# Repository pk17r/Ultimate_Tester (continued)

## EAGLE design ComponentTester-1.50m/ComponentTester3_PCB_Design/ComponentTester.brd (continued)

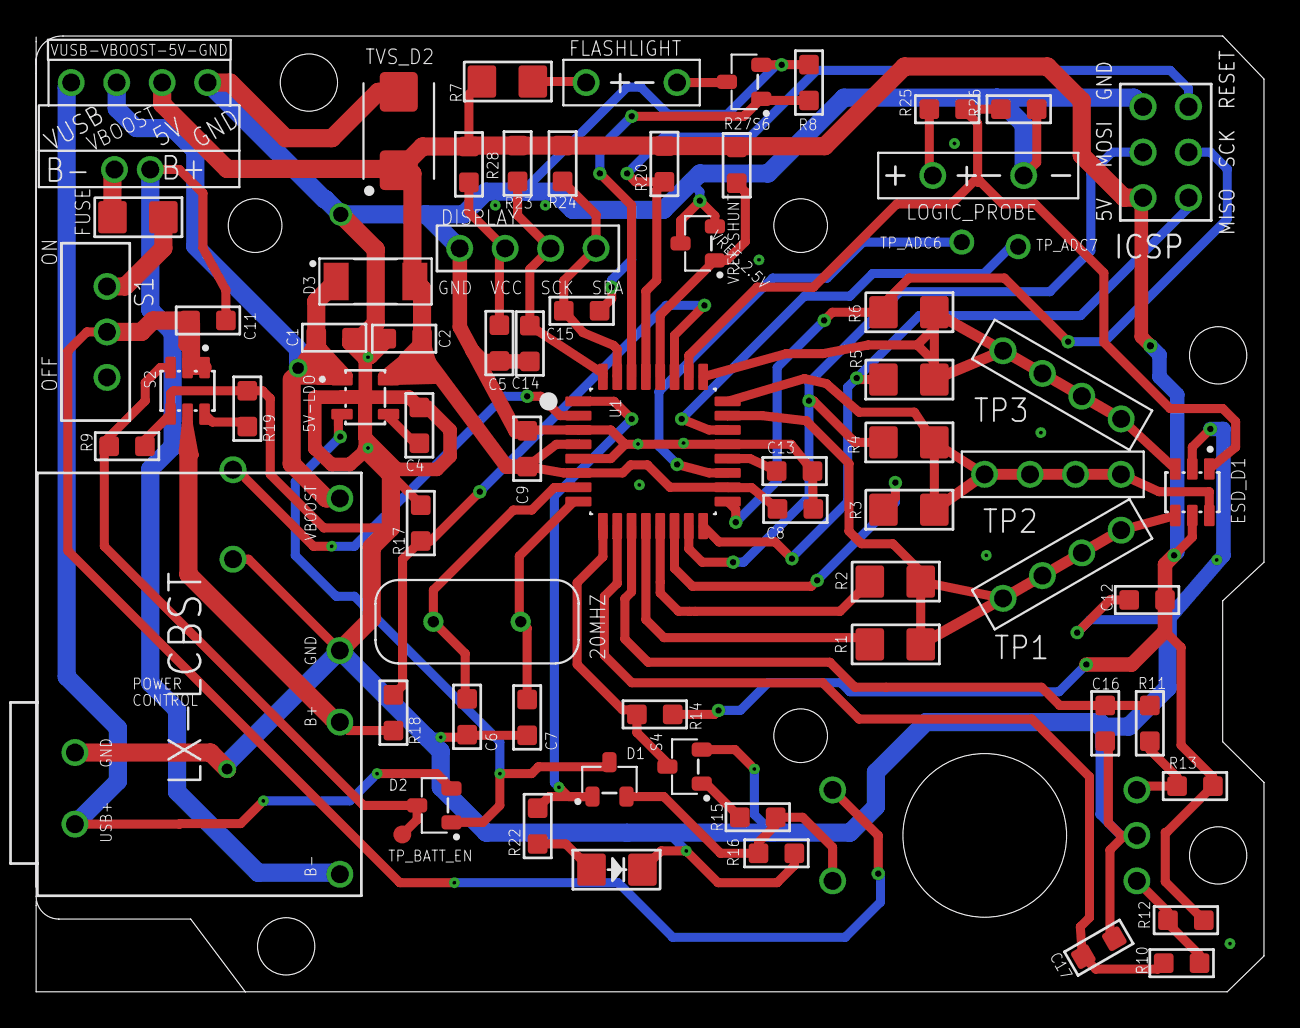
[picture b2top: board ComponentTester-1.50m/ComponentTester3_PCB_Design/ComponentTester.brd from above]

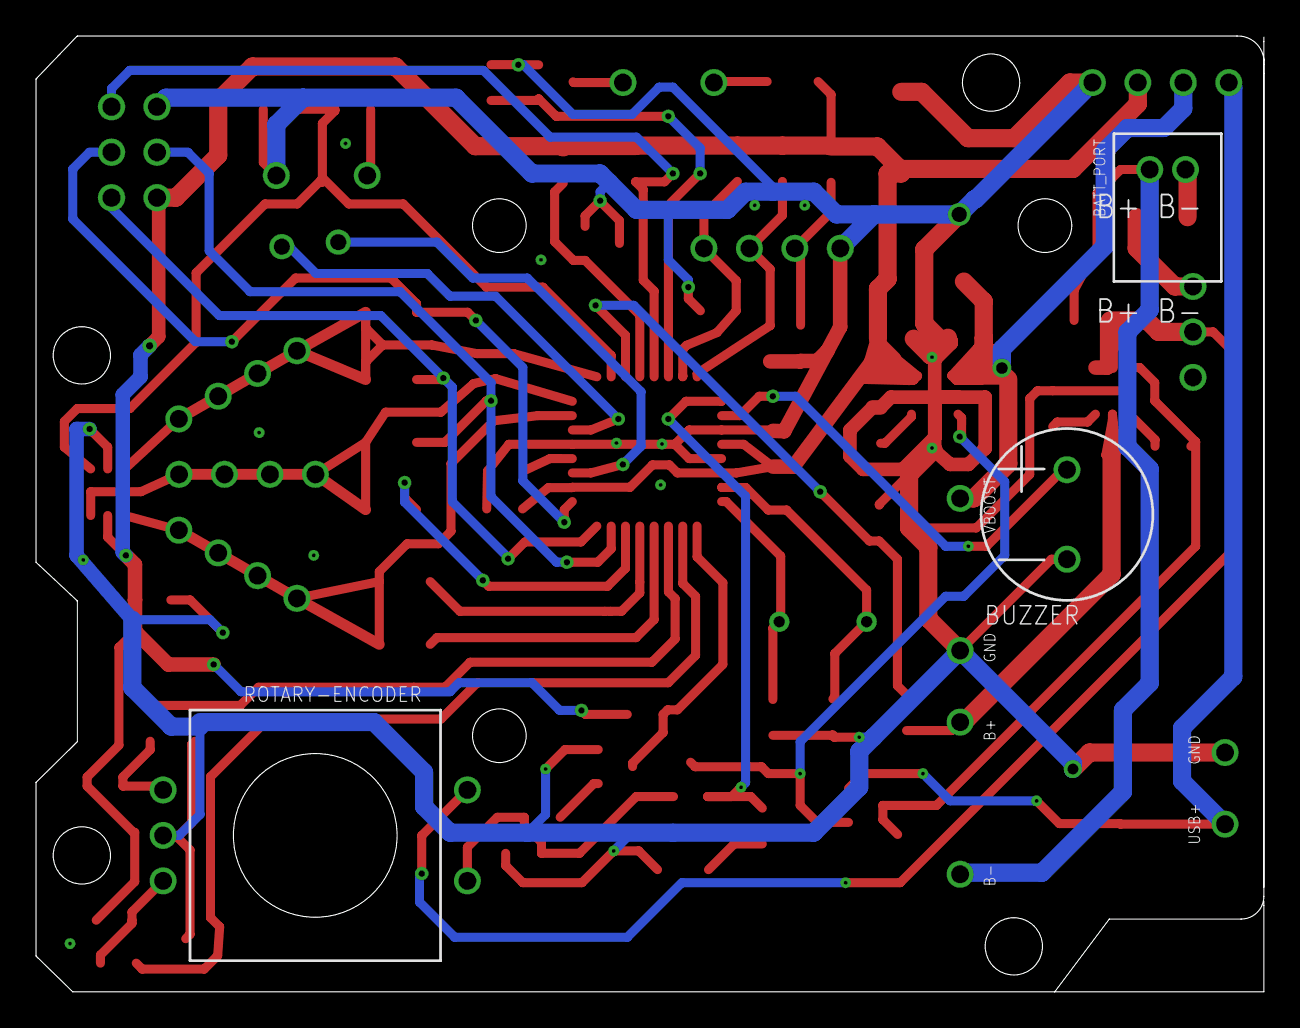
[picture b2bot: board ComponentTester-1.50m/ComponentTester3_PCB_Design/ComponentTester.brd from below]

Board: 2 copper layers, 68.6 x 53.4 mm, 72 parts (2 on the bottom side), 48 nets.

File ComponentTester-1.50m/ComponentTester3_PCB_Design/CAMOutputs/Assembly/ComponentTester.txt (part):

Partlist exported from D:/MyProjects/EAGLE/projects/ComponentTester3/ComponentTester.sch at 08-Nov-23 10:42 PM

Qty Value                         Device                                   Package                               Parts                                            Description                                                           AVAILABILITY CHECK_PRICES                                                                                 DATASHEET                                                         DESCRIPTION                                                                          DIGIKEY_PART_NUMBER    LOCATION MF                MP                 PACKAGE                    POS PRICE PURCHASE-URL                                                                                                                                                    SNAPEDA_LINK                                                                                  VALUE         
1                                 BATTERY-CHARGER-BOOST-MODULE-LX-LCBST    BATTERY-CHARGER-BOOST-MODULE-LX-LCBST CHARGE_BOOST                                     LX-LCBST_LIPO_CHARGER_BOOST                                                                                                                                                                                                                                                                                                                                                                                                                                                                                                                                                                                                                                                                                                  
1                                 DISPLAY-1.3"-SH1106-I2C                  DISPLAY-1.3"-SH1106-I2C               DISPLAY                                          SH1106 I2C DISPLAY                                                                                                                                                                                                                                                                                                                                                                                                                                                                                                                                                                                                                                                                                                           
2   100K                          RESISTOR_SMD0603                         0603                                  R8, R14                                          resistor smd                                                                                                                                                                                                                                                                                                                                                                                                                                                                                                                                                                                                                                                                                                                 
1   100K(OP)                      RESISTOR_SMD0603                         0603                                  R9                                               resistor smd                                                                                                                                                                                                                                                                                                                                                                                                                                                                                                                                                                                                                                                                                                                 
4   100nF                         CAPACITOR_SMD0603                        0603                                  C8, C9, C16, C17                                 capacitor 1206                                                                                                                                                                                                                                                                                                                                                                                                                                                                                                                                                                                                                                                                                                               
10  10K                           RESISTOR_SMD0603                         0603                                  R10, R11, R12, R13, R15, R18, R19, R20, R25, R27 resistor smd                                                                                                                                                                                                                                                                                                                                                                                                                                                                                                                                                                                                                                                                                                                 
1   10nF-C0G-NP0                  CAPACITOR_SMD0603                        0603                                  C4                                               capacitor 1206                                                                                                                                                                                                                                                                                                                                                                                                                                                                                                                                                                                                                                                                                                               
1   10uF                          CAPACITOR_SMD0603                        0603                                  C12                                              capacitor 1206                                                                                                                                                                                                                                                                                                                                                                                                                                                                                                                                                                                                                                                                                                               
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
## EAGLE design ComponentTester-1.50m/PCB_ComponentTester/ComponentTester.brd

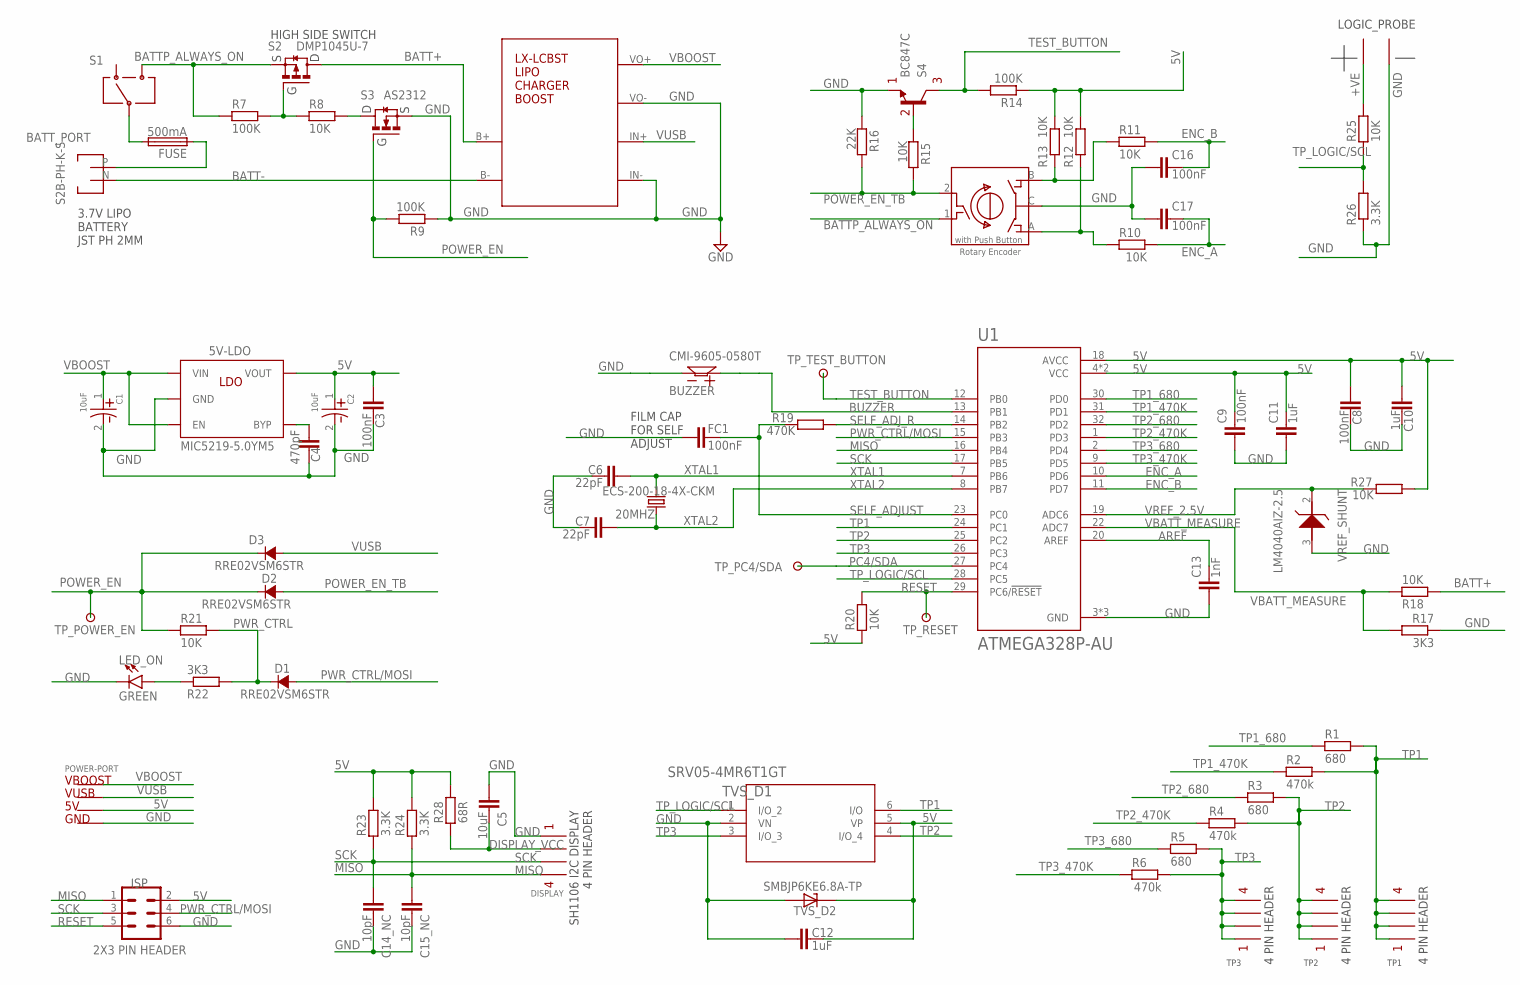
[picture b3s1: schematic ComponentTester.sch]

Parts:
5V-LDO: MIC5219-5.0YM5; SOT-23-5
20MHZ: ECS-200-18-4X-CKM; XTAL_ECS-200-18-4X-CKM
BATT_PORT: S2B-PH-K-S
BUZZER: CMI-9605-0580T; BUZZER_CMI-9605-0580T
C1, C2: 10uF; 1206_DIRECTED
C3, C16, C17: 100nF; 0603
C4: 470pF; 0603
C5: 10uF; 0603
C6, C7: 22pF; 0603
C8, C9: 100nF; 1206
C10, C11: 1uF; 1206
C12: 1uF; 0603
C13: 1nF; 0603
C14_NC, C15_NC: 10pF; 0603
CHARGE_BOOST: LX-LCBST_LIPO_CHARGER_BOOST
D1, D2, D3: RRE02VSM6STR; TUMD2SM-2
DISPLAY: SH1106_I2C_DISPLAY; SH1106_1.3IN_I2C_DISPLAY
ENC: PEC12R-3217F-S0024-ND; PEC12R-3217F-S0024
FC1: 100nF; 0805
FUSE: 500mA; 1206
ISP: 2X3 PIN HEADER; ISP_HEADER
LED_ON: GREEN; 1206_DIODE
LOGIC_PROBE: 5MM_PIN_HEADER
POWER-PORT: POWER_OUT_4_PIN_HEADER
R1, R3, R5: 680; 1206
R2, R4, R6: 470k; 1206
R7, R9, R14: 100K; 0603
R8, R10, R11, R12, R13, R15, R18, R20, R21, R27: 10K; 0603
R16: 22K; 0603
R17, R22: 3K3; 0603
R19: 470K; 0603
R23, R24: 3.3K; 0603
R25: 10K; 1206
R26: 3.3K; 1206
R28: 68R; 0603
S1: SLW-913535-2A-RA-D
S2: DMP1045U-7; SOT-23-3
S3: AS2312; SOT-23-3
S4: BC847C; SOT-23-3
TP1, TP2, TP3: 4_PIN_HEADER
TP_PC4/SDA: TEST_POINT
TP_POWER_EN: TEST_POINT
TP_RESET: TEST_POINT
TP_TEST_BUTTON: TEST_POINT
TVS_D1: SRV05-4MR6T1GT; TSOP6_3P1X1P7_ONS
TVS_D2: SMBJP6KE6.8A-TP; DIOM5336X244N
U1: ATMEGA328P-AU; QFP80P900X900X120-32N
VREF_SHUNT: LM4040AIZ-2.5; TO92-3

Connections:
5V: 5V-LDO.5 (VOUT), C2.1, C3.2, C8.2, C9.1, C10.2, C11.1, C12.1, ISP.2, POWER-PORT.5V, R12.2, R13.2, R14.1, R20.1, R23.2, R24.2, R27.1, R28.2, TVS_D1.5 (VP), TVS_D2.C, U1.4 (VCC), U1.6 (VCC), U1.18 (AVCC)
+VE: LOGIC_PROBE.P$1, R25.2
AREF: C13.1, U1.20 (AREF)
BATT+: CHARGE_BOOST.B+, R18.2, S2.3 (D)
BATT+_PORT: BATT_PORT.P, FUSE.1
BATT-: BATT_PORT.N, CHARGE_BOOST.B-
BATTP_ALWAYS_ON: ENC.1, R7.1, S1.3, S2.2 (S)
BUZZER: BUZZER.P$1, U1.13 (PB1)
BYP: 5V-LDO.4 (BYP), C4.2
DISPLAY_VCC: C5.1, DISPLAY.VCC, R28.1
ENC_A: C17.1, R10.2, U1.10 (PD6)
ENC_B: C16.1, R11.2, U1.11 (PD7)
FUSE_2_SWITCH: FUSE.2, S1.2
GND: 5V-LDO.2 (GND), BUZZER.P$2, C1.2 (N), C2.2 (N), C3.1, C4.1, C5.2, C6.1, C7.1, C8.1, C9.2, C10.1, C11.2, C12.2, C13.2, C14_NC.1, C15_NC.1, C16.2, C17.2, CHARGE_BOOST.IN- (USB-), CHARGE_BOOST.VO-, DISPLAY.GND, ENC.C, FC1.1, ISP.6, LED_ON.C, LOGIC_PROBE.P$2, POWER-PORT.GND, R9.1, R16.1, R17.1, R26.1, S3.2 (S), S4.2 (E), TVS_D1.2 (VN), TVS_D2.A, U1.3 (GND), U1.5 (GND), U1.21 (GND), VREF_SHUNT.3 (A)
MISO: C15_NC.2, DISPLAY.SDA, ISP.1, R24.1, U1.16 (PB4)
unnamed: ENC.B, R11.1, R13.1
unnamed: ENC.A, R10.1, R12.1
unnamed: R15.1, S4.1 (B)
NMOS_DRAIN: R8.2, S3.3 (D)
PC4/SDA: TP_PC4/SDA.P$1, U1.27 (PC4)
PMOS_GATE: R7.2, R8.1, S2.1 (G)
POWER_EN: D2.C, D3.C, R9.2, R21.1, S3.1 (G), TP_POWER_EN.P$1
POWER_EN_TB: D2.A, ENC.2, R15.2, R16.2
PWR_CTRL: D1.C, R21.2, R22.2
PWR_CTRL/MOSI: D1.A, ISP.4, U1.15 (PB3)
RESET: ISP.5, R20.2, TP_RESET.P$1, U1.29 (PC6/!RESET)
SCK: C14_NC.2, DISPLAY.SCK, ISP.3, R23.1, U1.17 (PB5)
SELF_ADJUST: FC1.2, R19.2, U1.23 (PC0)
SELF_ADJ_R: R19.1, U1.14 (PB2)
TEST_BUTTON: R14.2, S4.3 (C), TP_TEST_BUTTON.P$1, U1.12 (PB0)
TO_LED: LED_ON.A, R22.1
TP1: R1.2, R2.2, TP1.P$1, TP1.P$2, TP1.P$3, TP1.P$4, TVS_D1.6 (I/O), U1.24 (PC1)
TP1_470K: R2.1, U1.31 (PD1)
TP1_680: R1.1, U1.30 (PD0)
TP2: R3.2, R4.2, TP2.P$1, TP2.P$2, TP2.P$3, TP2.P$4, TVS_D1.4 (I/O_4), U1.25 (PC2)
TP2_470K: R4.1, U1.1 (PD3)
TP2_680: R3.1, U1.32 (PD2)
TP3: R5.2, R6.2, TP3.P$1, TP3.P$2, TP3.P$3, TP3.P$4, TVS_D1.3 (I/O_3), U1.26 (PC3)
TP3_470K: R6.1, U1.9 (PD5)
TP3_680: R5.1, U1.2 (PD4)
TP_LOGIC/SCL: R25.1, R26.2, TVS_D1.1 (I/O_2), U1.28 (PC5)
VBATT_MEASURE: R17.2, R18.1, U1.22 (ADC7)
VBOOST: 5V-LDO.1 (VIN), 5V-LDO.3 (EN), C1.1, CHARGE_BOOST.VO+, POWER-PORT.VBOOST
VREF_2.5V: R27.2, U1.19 (ADC6), VREF_SHUNT.2 (C)
VUSB: CHARGE_BOOST.IN+ (USB+), D3.A, POWER-PORT.VUSB
XTAL1: 20MHZ.2, C6.2, U1.7 (PB6)
XTAL2: 20MHZ.1, C7.2, U1.8 (PB7)

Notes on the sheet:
3.7V LIPO BATTERY JST PH 2MM
FILM CAP FOR SELF ADJUST
HIGH SIDE SWITCH

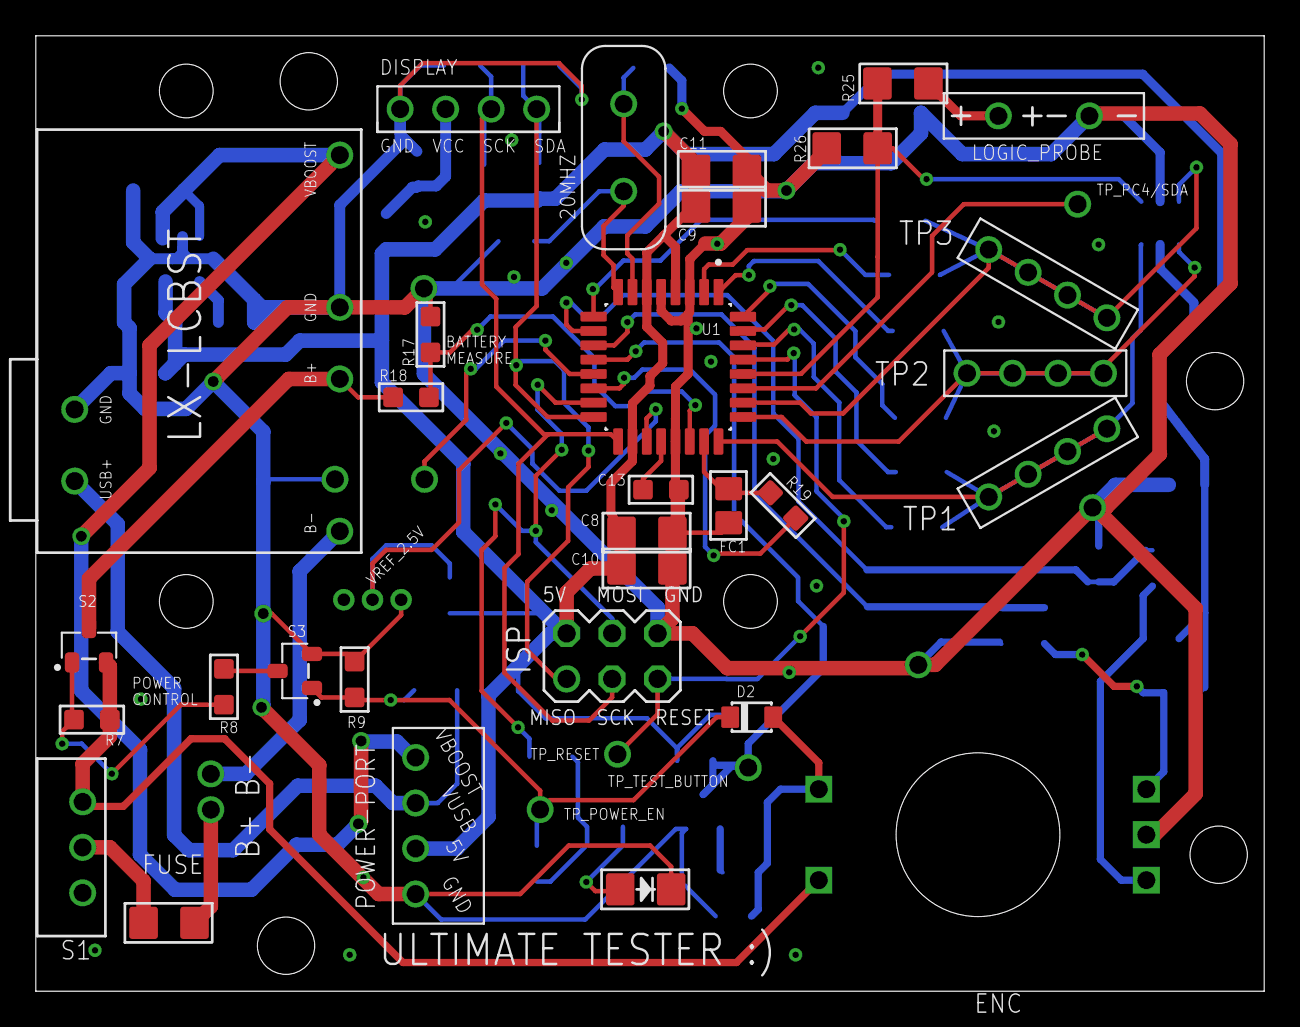
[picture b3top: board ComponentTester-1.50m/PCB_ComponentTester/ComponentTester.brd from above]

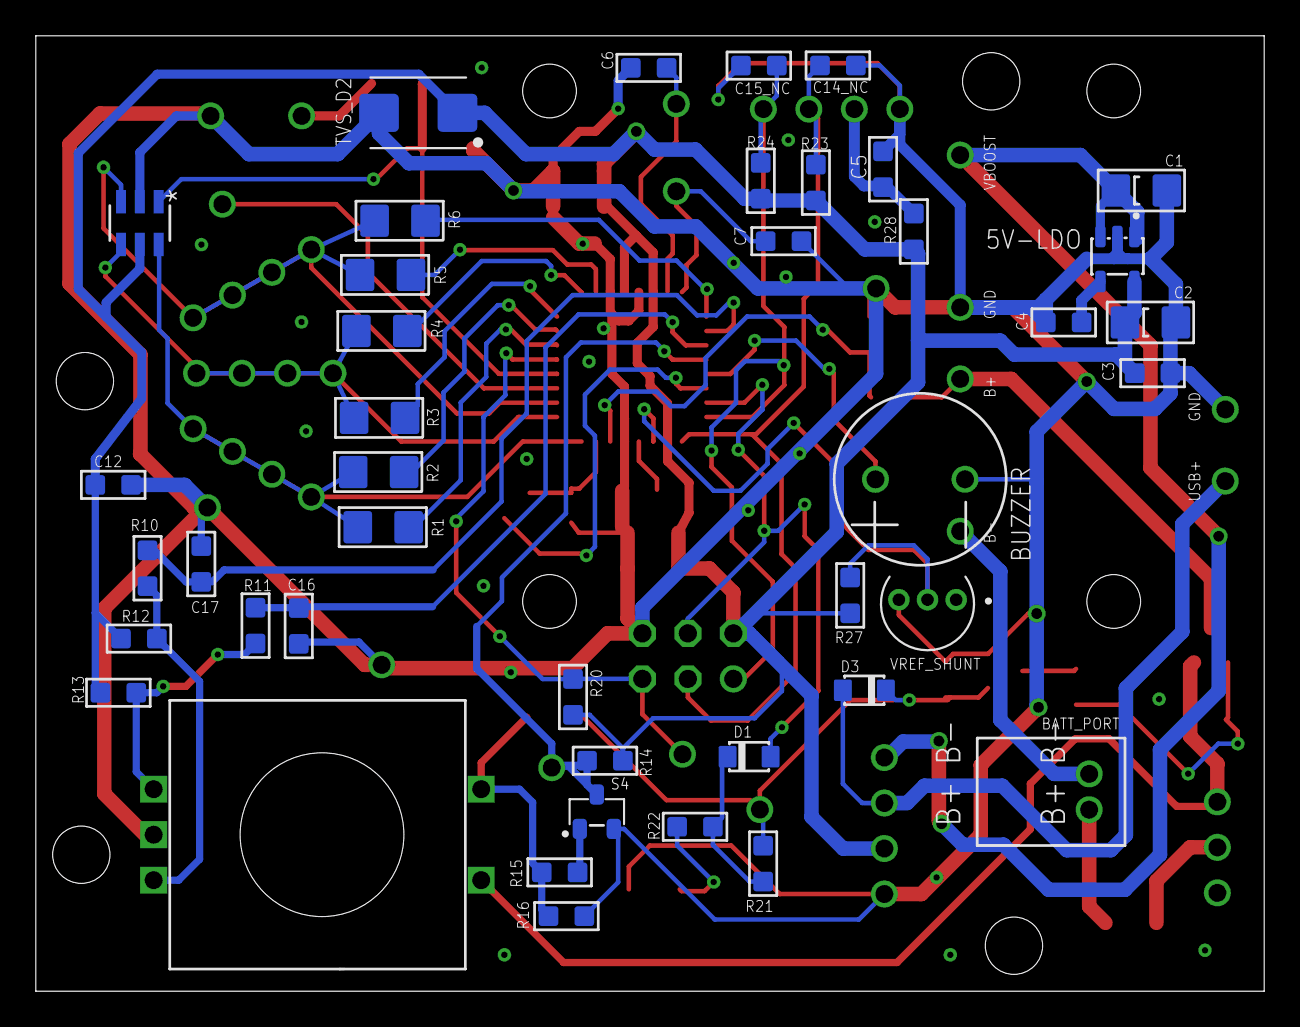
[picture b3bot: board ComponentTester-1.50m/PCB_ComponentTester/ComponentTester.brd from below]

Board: 2 copper layers, 68.6 x 53.3 mm, 76 parts (41 on the bottom side), 47 nets.

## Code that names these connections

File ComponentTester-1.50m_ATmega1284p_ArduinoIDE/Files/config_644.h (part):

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#define LCD_PORT         PORTB          /* port data register */
#define LCD_DDR          DDRB           /* port data direction register */
//#define LCD_DB_STD                      /* use standard pins 0-3 for DB4-7 */
#define LCD_DB4          PB4            /* port pin used for DB4 */
#define LCD_DB5          PB5            /* port pin used for DB5 */
#define LCD_DB6          PB6            /* port pin used for DB6 */
#define LCD_DB7          PB7            /* port pin used for DB7 */
#define LCD_RS           PB2            /* port pin used for RS */
#define LCD_EN1          PB3            /* port pin used for E */
/* display settings */
#define LCD_CHAR_X       16             /* characters per line */
#define LCD_CHAR_Y       2              /* number of lines */
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/* control and data lines */
#define LCD_PORT         PORTB          /* port data register */
#define LCD_DDR          DDRB           /* port data direction register */
#define LCD_RES          PB2            /* port pin used for /RESX (optional) */
#define LCD_CS           PB4            /* port pin used for /CSX (optional) */
#define LCD_DC           PB3            /* port pin used for D/CX */
#define LCD_SCL          PB7            /* port pin used for SCL */
#define LCD_SDA          PB5            /* port pin used for SDA/SDIO */
/* display settings */
#define LCD_DOTS_X       128            /* number of horizontal dots */
#define LCD_DOTS_Y       128            /* number of vertical dots */
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/* control and data lines */
#define LCD_PORT         PORTB          /* port data register */
#define LCD_DDR          DDRB           /* port data direction register */
#define LCD_RES          PB2            /* port pin used for /RES (optional) */
#define LCD_CS           PB4            /* port pin used for /CS (optional) */
#define LCD_DC           PB3            /* port pin used for D/C */
#define LCD_SCK          PB7            /* port pin used for SCK */
#define LCD_SDI          PB5            /* port pin used for SDI (data input) */
//#define LCD_SDO          PB6            /* port pin used for SDO (data output) */
/* display settings */
#define LCD_DOTS_X       320            /* number of horizontal dots */
#define LCD_DOTS_Y       240            /* number of vertical dots */
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/* control lines */
#define LCD_PORT         PORTC          /* port data register */
#define LCD_DDR          DDRC           /* port data direction register */
#define LCD_RES          PC4            /* port pin used for /RESX (optional) */
#define LCD_CS           PC3            /* port pin used for /CSX (optional) */
#define LCD_DC           PC2            /* port pin used for D/CX */
#define LCD_WR           PC1            /* port pin used for WRX */
#define LCD_RD           PC0            /* port pin used for RDX (optional) */
/* data lines DB0-7 */
#define LCD_PORT2        PORTB          /* port data register */
#define LCD_DDR2         DDRB           /* port data direction register */
#define LCD_PIN2         PINB           /* port data direction register */
#define LCD_DB0          PB0            /* port pin used for DB0 */
#define LCD_DB1          PB1            /* port pin used for DB1 */
#define LCD_DB2          PB2            /* port pin used for DB2 */
#define LCD_DB3          PB3            /* port pin used for DB3 */
#define LCD_DB4          PB4            /* port pin used for DB4 */
#define LCD_DB5          PB5            /* port pin used for DB5 */
#define LCD_DB6          PB6            /* port pin used for DB6 */
#define LCD_DB7          PB7            /* port pin used for DB7 */
/* display settings */
#define LCD_DOTS_X       320            /* number of horizontal dots */
#define LCD_DOTS_Y       480            /* number of vertical dots */
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/* control and data lines */
#define LCD_PORT         PORTB          /* port data register */
#define LCD_DDR          DDRB           /* port data direction register */
#define LCD_RES          PB2            /* port pin used for /RES (optional) */
#define LCD_CS           PB4            /* port pin used for /CS (optional) */
#define LCD_DC           PB3            /* port pin used for D/C */
#define LCD_SCL          PB7            /* port pin used for SCL */
#define LCD_SDA          PB5            /* port pin used for DIN/SDA (data input) */
//#define LCD_SDO          PB6            /* port pin used for DOUT/SDO (data output) */
/* display settings */
#define LCD_DOTS_X       320            /* number of horizontal dots */
#define LCD_DOTS_Y       480            /* number of vertical dots */
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/* control and data lines */
#define LCD_PORT         PORTB          /* port data register */
#define LCD_DDR          DDRB           /* port data direction register */
#define LCD_RES          PB2            /* port pin used for /RES (optional) */
#define LCD_SCE          PB4            /* port pin used for /SCE (optional) */
#define LCD_DC           PB3            /* port pin used for D/C */
#define LCD_SCLK         PB7            /* port pin used for SCLK */
#define LCD_SDIN         PB5            /* port pin used for SDIN (data input) */
/* display settings */
#define LCD_DOTS_X       84             /* number of horizontal dots */
#define LCD_DOTS_Y       48             /* number of vertical dots */
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/* control and data lines */
#define LCD_PORT         PORTB          /* port data register */
#define LCD_DDR          DDRB           /* port data direction register */
#define LCD_RESET        PB2            /* port pin used for /RES */
#define LCD_CS           PB4            /* port pin used for /CS (optional) */
#define LCD_SCLK         PB7            /* port pin used for SCLK */
#define LCD_SDIN         PB5            /* port pin used for SDIN (data input) */
/* display settings */
#define LCD_DOTS_X       96             /* number of horizontal dots */
#define LCD_DOTS_Y       65             /* number of vertical dots */
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/* control and data lines */
#define LCD_PORT         PORTB          /* port data register */
#define LCD_DDR          DDRB           /* port data direction register */
#define LCD_RESET        PB2            /* port pin used for /RES (optional) */
#define LCD_CS           PB4            /* port pin used for /CS (optional) */
#define LCD_A0           PB3            /* port pin used for A0 */
#define LCD_SCL          PB7            /* port pin used for SCL */
#define LCD_SI           PB5            /* port pin used for SI (data input) */
/* display settings */
#define LCD_DOTS_X       128            /* number of horizontal dots */
#define LCD_DOTS_Y       64             /* number of vertical dots */
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/* control and data lines */
#define LCD_PORT         PORTB          /* port data register */
#define LCD_DDR          DDRB           /* port data direction register */
#define LCD_RESET        PB2            /* port pin used for /RES (optional) */
#define LCD_CS           PB4            /* port pin used for /CS (optional) */
#define LCD_SCL          PB7            /* port pin used for SCL */
#define LCD_SI           PB5            /* port pin used for SI (data input) */
/* display settings */
#define LCD_DOTS_X       128            /* number of horizontal dots */
#define LCD_DOTS_Y       64             /* number of vertical dots */
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/* control lines */
//#define LCD_PORT         PORTB          /* port data register */
//#define LCD_DDR          DDRB           /* port data direction register */
//#define LCD_RESET        PB2            /* port pin used for /RES (optional) */
/* display settings */
#define LCD_DOTS_X       128            /* number of horizontal dots */
#define LCD_DOTS_Y       64             /* number of vertical dots */
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/* control and data lines */
#define LCD_PORT         PORTB          /* port data register */
#define LCD_DDR          DDRB           /* port data direction register */
#define LCD_RESET        PB2            /* port pin used for /RES (optional) */
#define LCD_CS           PB4            /* port pin used for /CS (optional) */
#define LCD_DC           PB3            /* port pin used for D/C */
#define LCD_SCLK         PB7            /* port pin used for SCLK */
#define LCD_SDIN         PB5            /* port pin used for SDIN (data input) */
/* display settings */
#define LCD_DOTS_X       128            /* number of horizontal dots */
#define LCD_DOTS_Y       64             /* number of vertical dots */
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/* control and data lines */
#define LCD_PORT         PORTB          /* port data register */
#define LCD_DDR          DDRB           /* port data direction register */
#define LCD_RESET        PB2            /* port pin used for /RES (optional) */
#define LCD_CS           PB4            /* port pin used for /CS (optional) */
#define LCD_SCLK         PB7            /* port pin used for SCLK */
#define LCD_SDIN         PB5            /* port pin used for SDIN (data input) */
/* display settings */
#define LCD_DOTS_X       128            /* number of horizontal dots */
#define LCD_DOTS_Y       64             /* number of vertical dots */
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
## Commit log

2023-09-08 Firmware 1.50-m on Arduino Uno
    Correct Readings of Resistors within 1%: 220, 330, 470, 1k, 2.2k,
    220k, 470k, 1M.
    Incorrect Readings of Resistors: 10 as 5, 100 as 50, 4.7k as 14k,
    10k as 4.2k, 22k as 9.9k, 47k as 21.5k, 100k as 44k
2023-09-08 Flashlight and Power Light working now
2023-09-09 Using ADC_LARGE_BUFFER_CAP for Uno and text center align
    Arduino Uno has a bigger AREF cap of 100nF than what program
    demands of 1nF. In config.h turned on:
    define ADC_LARGE_BUFFER_CAP /* 100nF cap at AREF */
2023-09-09 Passive buzzer and Continuity Check now working
2023-09-09 moved code to Flash, turned on various features
2023-09-10 Working version on ATmega1284P MCU
2023-09-11 Added battery measurement, SH1106 display
2023-09-12 Moved Test Button to Port B, PB0
    As PC7 was having interference with neighbor pin AVCC
    and unable to turn LOW
2023-09-12 Add note on Flash Procedure for new MCU and correct VREF V
2023-09-19 Changed Logic Probe resistors & new Flashlight circuit
    Logic Probes now 47K and 220K
    Added a BJT and higher current LED, with separate pin
    than Buzzer
2023-09-23 Added ST7735 COLOR Display, moved flashlight to PC1
2023-09-23 Added monitoring of USB_Voltage
2023-09-23 Added USB V Display String on UI
2023-09-25 Measure USB Voltage on 1284p and backup
2023-09-26 Removed USB V Sense pin. Moved to ATMEGA 328 & Non Color Display
2023-09-30 Removed USBV voltage measure
2023-09-30 removed USBV changes from main.c
2023-09-30 Config update
2023-11-03 Working version on 328p PCB
2023-11-03 Removed unused project
2023-11-03 Project folder rename
2023-11-03 Renamed Arduino IDE project folder
2023-11-03 Added Eagle PCB Files
2023-11-03 Mounting Hole correction on PCB
2023-11-09 PCB 3 Design
2023-12-01 Added VOUT measure and No Component Found Correction
    VOUT is Battery Boost voltage
    No Component string increased in size so that
    the question mark does not overwrite 't' of
    'No component' string.
2023-12-02 Added Current Measurement Menu Item
2023-12-02 Improved Current Sense, Added auto detect USB
2023-12-06 Added adjustment of VIoffset
2023-12-07 Selecting options.
2023-12-07 Adding LiBatteryChargeBoostBoard PCB & Schematics
2023-12-11 Ultimate Tester name & Power measure addition
2023-12-17 Minor Offset value adjustments & added VIN
2023-12-18 Adding LiBatteryChargeBoostBoard_v1_PCB
2023-12-18 Renamed LiBatteryChargeBoostBoard_v1_PCB.zip_PCB to UltimateTester_PCB
2023-12-18 Add BOM and Schematics to Ultimate Tester zip file
2024-01-20 Removed Lower limit on VOUT
    Not needed as added a separate 6V boost for
    Component Tester circuit
2024-03-18 Readme update
2024-12-26 Add Shunt Current Sensor INA226
2024-12-26 Simplify and correct Bit-Bang I2C Read and Write
2024-12-26 Change Font from 8x8 to 8x16 -> Bigger
2024-12-26 Power Meter: Clear only values and slow down update
2024-12-26 Power Meter: Reduce number of clears
2024-12-27 INA226 corrections, reduction in I2C file size, config changes
2024-12-27 Add IOut active symbol
2024-12-28 Power Meter improvements
2024-12-28 Reduce Power Meter flash usage
2024-12-28 Move to Component Tester version m1.54
2024-12-28 Improved I2C
2024-12-28 I2C Improvements
2024-12-28 I2C BitBang Start, Repeated Start and Stop conditions improved
2024-12-28 new board config files
2024-12-30 Added External Power Symbol and Ext Pow/Batt voltage in Power Meter
2024-12-30 Add INA 226 Bus Voltage Offset Multiplier Calibrated Value
2024-12-30 Reduce INA226 memory size by removing floats and C files like fabs()
2024-12-30 Add Test Component Menu Item
2024-12-30 INA226 Long Press to zero Current Value
2024-12-30 Add External Power font characters for 8x12 and 8x16 vpf fonts
2024-12-30 Increase turnoff timeout to 2 mins
2024-12-30 Use timeout in I2C.c file
2024-12-30 Config file option selections
2024-12-30 Change Menu First Line to Show Battery
2025-01-01 Documentation and binaries
2025-01-03 Add configs and changes for Mega2560 with ST7735 on breadboard
2025-01-03 INA226 Power Meter: Make IOffset_local as static
2025-01-03 Remove INA_226_SELF_ADJUST_CURRENT Functionality
2025-01-03 Revert I2C.c, Replace Repeated I2C Start with I2C Stop Start
2025-01-03 Add license for INA226.c
2025-01-03 Rename 1.50m to 1.54m
2025-01-03 Cleanup
2025-01-03 Comments
2025-01-03 Add README and pre-processor statements for TP_LOGIC and BAT_NONE in Power Monitor
2025-01-03 Add pics to readme
2025-01-03 Add pic
2025-01-03 Readme
2025-01-05 Add buzzer beeps when power crosses threshold
2025-01-05 Add #define MAINMENU_SHOW_BATTERY_AT_TOP in config.h
2025-01-05 Reduce image sizes
2025-01-05 Remove some differences from 1.54m
2025-01-05 commit config and hex files project
2025-01-07 INA 226 default values for 100mOhm shunt and steps to calibrate module
2025-01-08 Modifications to INA226 calibration process and steps
2025-01-08 INA226 readme changes and more calibration step explanations
2025-01-08 Readme add power monitor accuracy
2025-01-08 update INA226 config recommendations
2025-01-08 Saving config files
2025-01-08 Remove debug print statements from INA226.c
2025-01-08 Remove commented functions from INA226.c
2025-01-08 Correct returns in INA226_Setup() that got in while debugging
2025-01-18 Increase Logic Probe Resistors -> Voltmeter
    Usable range 0-55V now
2025-02-02 Add SSD1309 1.54 inch OLED I2C Display
2025-02-23 Add averaging of INA226 samples
2025-03-08 Add 1284 config, config for External Power, Turn off Long Press Power Off
2025-03-08 Add INA3221 Power Monitor. Add HW_POWER_MONITOR flag
2025-03-09 Increase Power Monitor's Voltage Precision
    - Show 3 decimal places for voltage in Power Monitor instead of 2
    decimal places
    - Add POWER_MONITOR_AT_POWER_ON option in config.h, useful in
    development
2025-03-10 Correctly display 3 decimal digits for Voltage in Power Monitor
2025-06-28 Use SPI SH1107 Display and update INA3221 R to 40mOhm
2025-11-08 Save current configs - DIY 1284
2025-11-11 Config for Ultimate Tester v2 ^44PA and MP28167_A Driver
2025-11-11 MP28167_A I2C working now
2025-11-11 VOUT increase decrease working now
2025-11-11 Set Buzzer and Flashlight as output whenever they are turned on
2025-11-12 Change DC DC R1, faster disable at bootup
2025-11-22 Add MP28167_A_BUCK_BOOST_CONVERTER output disable using mosfet
2025-11-23 MP28167_A - Set Min Vout as 1.2V for stability
2025-11-23 Display ILimit on Power Monitor
2025-11-23 Ability to change Iout Limit
2025-11-23 MP28167_A UI enhancements
2025-11-23 disable Over Power Buzzer with MP28167_A
2025-11-23 Check Vout and ILimMax going outside limits Continously
2025-11-23 Turn off buck boost converter at power off
2025-11-23 Increase debounce time to 50ms
2025-11-26 Reorder main menu, Buck Boost new R1 R2
2025-12-07 Comment out SW_INITIAL_TEST_BTN_PRESS_DURATION_OPTIONS
2025-12-15 Add UltimateTester_v2.1 PCB, Schematics. Add About Page
2025-12-15 Add Usage Page
2025-12-27 Remove duplicate files from tree folder
2025-12-27 better default values for 644pa
2025-12-27 Toolchain installations files and steps
2025-12-27 Ability to not have Contrast Adjustment in menu
2025-12-27 Hide Save menuitem and directly go into Save after Self Adjustment
2025-12-27 Add IZero computation in Self Adjustment
2025-12-27 Enable IOut during Self Adjustment
2025-12-27 Round I Zero Offset Adjustment to nearest 100 uA value
2025-12-27 Show TP2 at SQ Wave & PWM
2025-12-29 MP28167 Inc/Dec Vout by changing register val - best way
2025-12-29 MP28167_A cleaning
2025-12-30 rearrange menu
2025-12-30 correction in Vout, Vref and Vref register val ranges
2025-12-30 Add Fw Build Date and Time to About Page
2026-01-06 INA3221 corrections
2026-01-06 INA226 & adjust improvements
2026-06-13 Add voltage conversion functions to MP28167_A
2026-06-13 Disable Buck Boost Converter when output V goes over desired V
2026-06-13 Power and ILIM rows always show
2026-06-13 Real time Power Supply Status at top right corner, on all screens
2026-06-13 Update battery status on Main Menu in realtime
2026-06-14 Adjust IOutLimMax and Iout of Powersupply in real time from any screen
2026-06-14 Save hex
